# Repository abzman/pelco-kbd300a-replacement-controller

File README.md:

# pelco-kbd300a-replacement-controller
replacement board and code for this joystick and keyboard

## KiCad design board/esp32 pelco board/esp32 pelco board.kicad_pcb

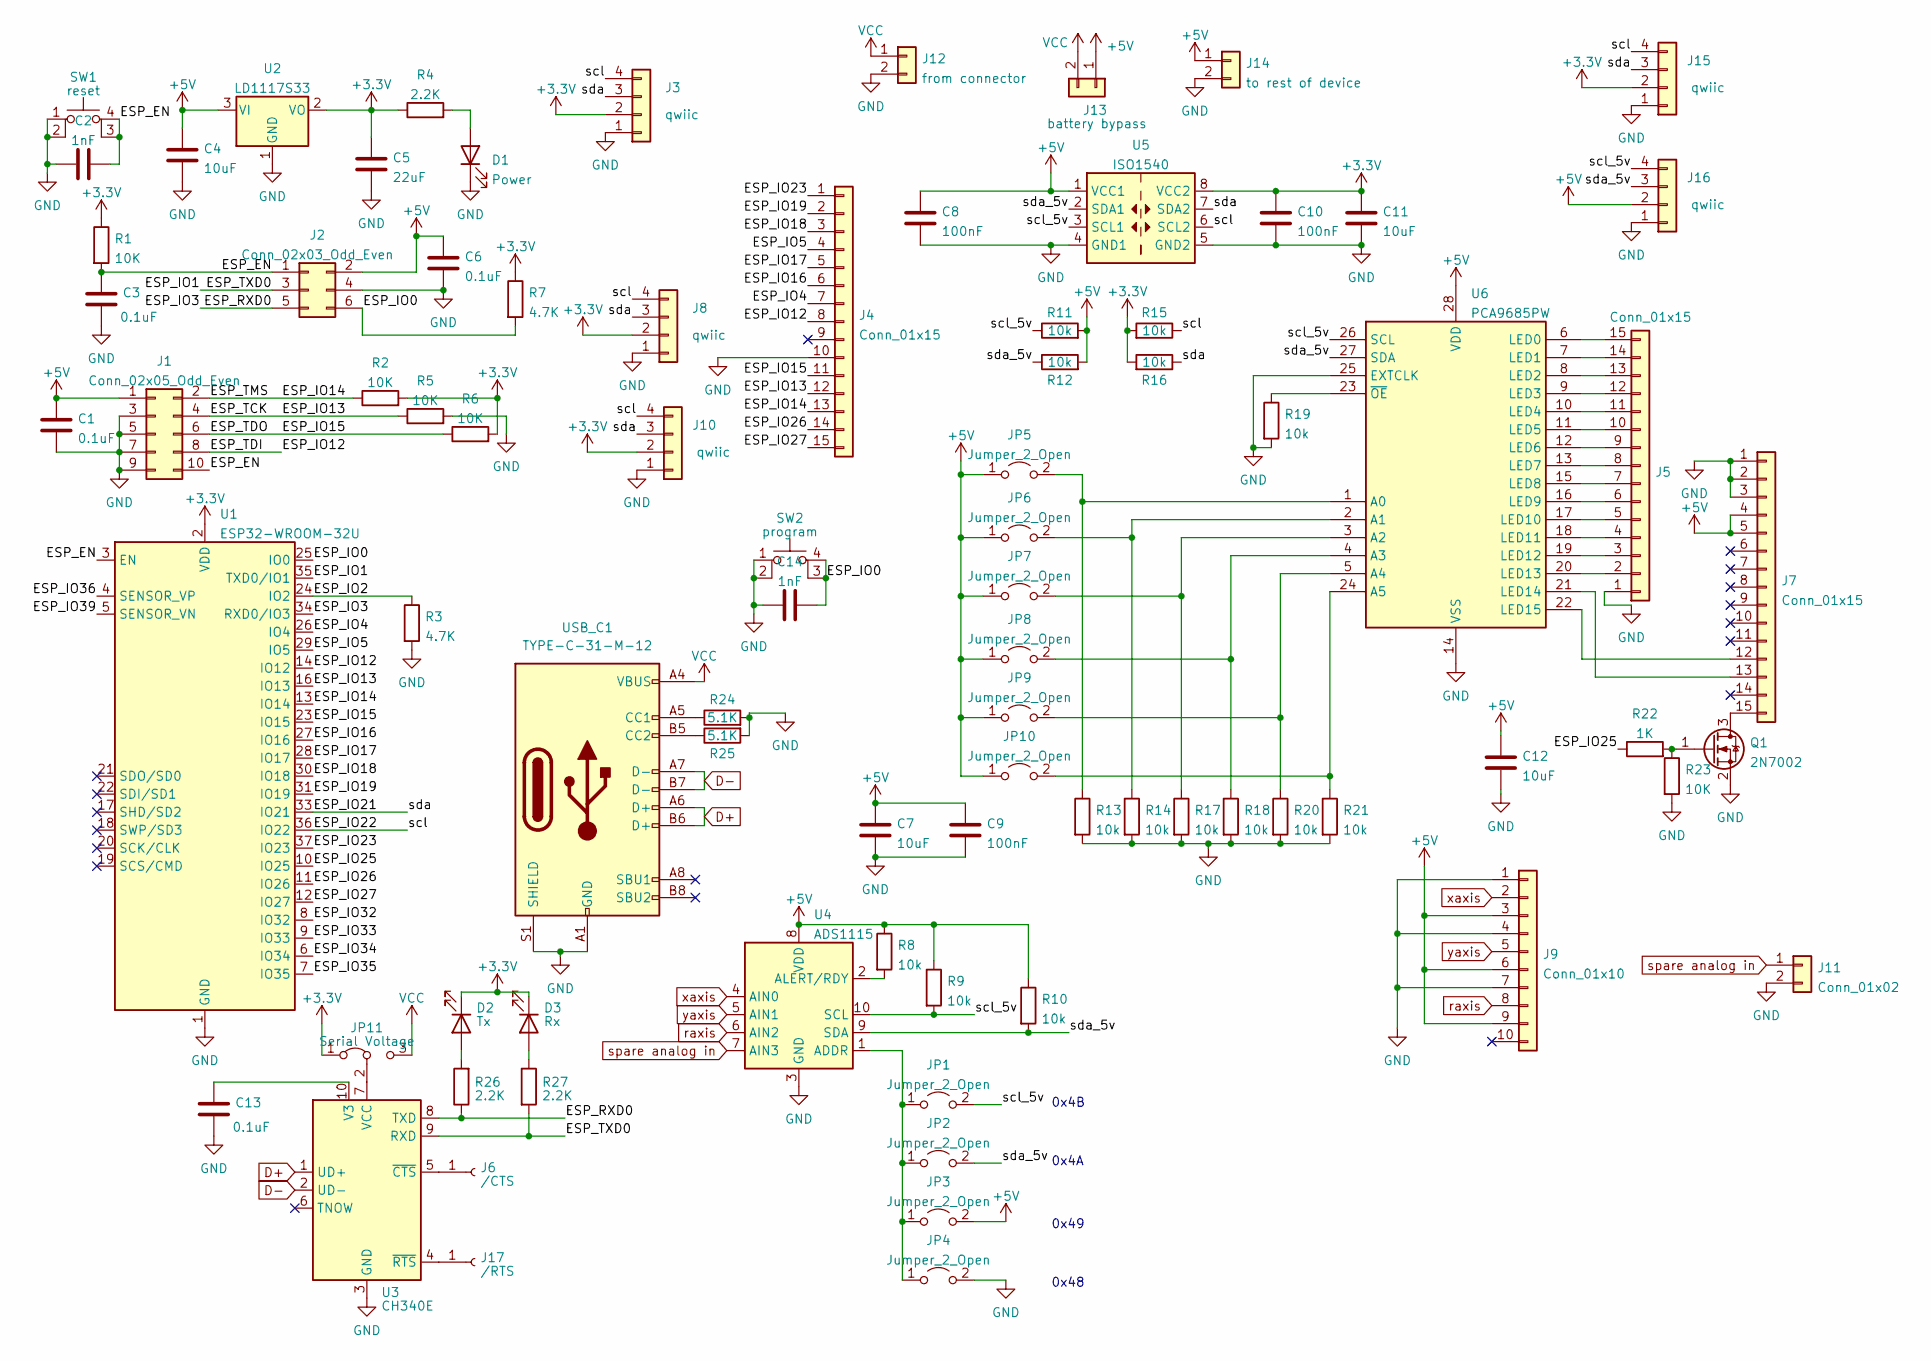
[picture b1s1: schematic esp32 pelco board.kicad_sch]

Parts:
C1, C3, C6, C13: 0.1uF; C_0603_1608Metric
C2, C14: 1nF; C_0603_1608Metric
C4: 10uF; CP_Radial_D5.0mm_P2.00mm
C5: 22uF; CP_Radial_D5.0mm_P2.00mm
C7, C11, C12: 10uF; C_0603_1608Metric
C8, C9, C10: 100nF; C_0603_1608Metric
D1: Power; LED_0603_1608Metric
D2: Tx; LED_0603_1608Metric
D3: Rx; LED_0603_1608Metric
J1: Conn_02x05_Odd_Even; IDC-Header_2x05_P2.54mm_Vertical
J2: Conn_02x03_Odd_Even; IDC-Header_2x03_P2.54mm_Vertical
J3, J8, J10, J15, J16: qwiic; JST_SH_SM04B-SRSS-TB_1x04-1MP_P1.00mm_Horizontal
J4, J5, J7: Conn_01x15; PinHeader_1x15_P2.54mm_Vertical
J6: /CTS; PinSocket_1x01_P2.54mm_Vertical
J9: Conn_01x10; PinHeader_1x10_P2.54mm_Vertical
J11: Conn_01x02; PinHeader_1x02_P2.54mm_Vertical
J12: from connector; PinHeader_1x02_P2.54mm_Vertical
J13: battery bypass; SolderJumper-2_P1.3mm_Bridged_RoundedPad1.0x1.5mm
J14: to rest of device; PinHeader_1x02_P2.54mm_Vertical
J17: /RTS; PinSocket_1x01_P2.54mm_Vertical
JP1, JP2, JP3, JP4, JP5, JP6, JP7, JP8, JP9, JP10: Jumper_2_Open; SolderJumper-2_P1.3mm_Open_RoundedPad1.0x1.5mm
JP11: Serial Voltage; SolderJumper-3_P1.3mm_Bridged12_RoundedPad1.0x1.5mm
Q1: 2N7002; SOT-23
R1, R2, R5, R6, R23: 10K; R_0603_1608Metric
R3, R7: 4.7K; R_0603_1608Metric
R4, R26, R27: 2.2K; R_0603_1608Metric
R8, R9, R10, R11, R12, R13, R14, R15, R16, R17, R18, R19, R20, R21: 10k; R_0603_1608Metric
R22: 1K; R_0603_1608Metric
R24, R25: 5.1K; R_0603_1608Metric
SW1: reset; SW_TH_Tactile_Omron_B3F-10xx
SW2: program; SW_TH_Tactile_Omron_B3F-10xx
U1: ESP32-WROOM-32U
U2: LD1117S33; SOT-223-3_TabPin2
U3: CH340E; MSOP-10_3x3mm_P0.5mm
U4: ADS1115; TSSOP-10_3x3mm_P0.5mm
U5: ISO1540; SOIC-8_3.9x4.9mm_P1.27mm
U6: PCA9685PW; TSSOP-28_4.4x9.7mm_P0.65mm
USB_C1: TYPE-C-31-M-12; USB_C_Receptacle_HRO_TYPE-C-31-M-12; LCSC C165948

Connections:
+3V3: C5.1, C10.1, C11.1, D2.1 (K), D3.1 (K), J3.2, J8.2, J10.2, J15.2, JP11.1 (A), R1.1, R2.2, R4.1, R6.2, R7.1, R15.2, R16.2, U1.2 (VDD), U2.2 (VO), U5.8 (VCC2)
+5V: C1.1, C4.1, C6.1, C7.1, C8.1, C9.1, C12.1, J1.1, J2.2, J7.4, J7.5, J9.3, J9.6, J9.9, J13.1, J14.1, J16.2, JP3.2 (B), JP5.1 (A), JP6.1 (A), JP7.1 (A), JP8.1 (A), JP9.1 (A), JP10.1 (A), R8.1, R9.1, R10.1, R11.2, R12.2, U2.3 (VI), U4.8 (VDD), U5.1 (VCC1), U6.28 (VDD)
/ESP_EN: C2.2, C3.1, J1.10, J2.1, R1.2, SW1.3 (K), SW1.4 (A), U1.3 (EN)
/ESP_IO0: C14.2, J2.6, R7.2, SW2.3 (K), SW2.4 (A), U1.25 (IO0)
/ESP_IO1: J2.3, R27.2, U1.35 (TXD0/IO1), U3.9 (RXD)
/ESP_IO2: R3.1, U1.24 (IO2)
/ESP_IO3: J2.5, R26.1, U1.34 (RXD0/IO3), U3.8 (TXD)
/ESP_IO4: J4.7, U1.26 (IO4)
/ESP_IO5: J4.4, U1.29 (IO5)
/ESP_IO12: J1.8, J4.8, U1.14 (IO12)
/ESP_IO13: J1.4, J4.12, R5.1, U1.16 (IO13)
/ESP_IO14: J1.2, J4.13, R2.1, U1.13 (IO14)
/ESP_IO15: J1.6, J4.11, R6.1, U1.23 (IO15)
/ESP_IO16: J4.6, U1.27 (IO16)
/ESP_IO17: J4.5, U1.28 (IO17)
/ESP_IO18: J4.3, U1.30 (IO18)
/ESP_IO19: J4.2, U1.31 (IO19)
/ESP_IO21: J3.3, J8.3, J10.3, J15.3, R16.1, U1.33 (IO21), U5.7 (SDA2)
/ESP_IO22: J3.4, J8.4, J10.4, J15.4, R15.1, U1.36 (IO22), U5.6 (SCL2)
/ESP_IO23: J4.1, U1.37 (IO23)
/ESP_IO25: R22.1, U1.10 (IO25)
/ESP_IO26: J4.14, U1.11 (IO26)
/ESP_IO27: J4.15, U1.12 (IO27)
/ESP_IO32: U1.8 (IO32)
/ESP_IO33: U1.9 (IO33)
/ESP_IO34: U1.6 (IO34)
/ESP_IO35: U1.7 (IO35)
/ESP_IO36: U1.4 (SENSOR_VP)
/ESP_IO39: U1.5 (SENSOR_VN)
/scl_5v: J16.4, JP1.2 (B), R9.2, R11.1, U4.10 (SCL), U5.3 (SCL1), U6.26 (SCL)
/sda_5v: J16.3, JP2.2 (B), R10.2, R12.1, U4.9 (SDA), U5.2 (SDA1), U6.27 (SDA)
D+: U3.1 (UD+), USB_C1.A6 (D+), USB_C1.B6 (D+)
D-: U3.2 (UD-), USB_C1.A7 (D-), USB_C1.B7 (D-)
GND: C1.2, C2.1, C3.2, C4.2, C5.2, C6.2, C7.2, C8.2, C9.2, C10.2, C11.2, C12.2, C13.2, C14.1, D1.1 (K), J1.3, J1.5, J1.7, J1.9, J2.4, J3.1, J3.MP, J4.10, J5.1, J7.1, J7.2, J7.3, J8.1, J8.MP, J9.1, J9.4, J9.7, J10.1, J10.MP, J11.2, J12.2, J14.2, J15.1, J15.MP, J16.1, J16.MP, JP4.2 (B), Q1.2 (S), R3.2, R5.2, R13.2, R14.2, R17.2, R18.2, R19.2, R20.2, R21.2, R23.2, R24.2, R25.2, SW1.1, SW1.2, SW2.1, SW2.2, U1.1 (GND), U1.15 (GND), U1.38 (GND), U1.39 (GND), U2.1 (GND), U3.3 (GND), U4.3 (GND), U5.4 (GND1), U5.5 (GND2), U6.14 (VSS), U6.25 (EXTCLK), USB_C1.A1 (GND), USB_C1.A12 (GND), USB_C1.B1 (GND), USB_C1.B12 (GND), USB_C1.S1 (SHIELD)
unnamed: D1.2 (A), R4.2
unnamed: D2.2 (A), R26.2
unnamed: D3.2 (A), R27.1
unnamed: J5.2, U6.20 (LED13)
unnamed: J5.3, U6.19 (LED12)
unnamed: J5.4, U6.18 (LED11)
unnamed: J5.5, U6.17 (LED10)
unnamed: J5.6, U6.16 (LED9)
unnamed: J5.7, U6.15 (LED8)
unnamed: J5.8, U6.13 (LED7)
unnamed: J5.9, U6.12 (LED6)
unnamed: J5.10, U6.11 (LED5)
unnamed: J5.11, U6.10 (LED4)
unnamed: J5.12, U6.9 (LED3)
unnamed: J5.13, U6.8 (LED2)
unnamed: J5.14, U6.7 (LED1)
unnamed: J5.15, U6.6 (LED0)
unnamed: J6.1, U3.5 (~CTS)
unnamed: J7.12, U6.22 (LED15)
unnamed: J7.13, U6.21 (LED14)
unnamed: J7.15, Q1.3 (D)
unnamed: J17.1, U3.4 (~RTS)
unnamed: JP1.1 (A), JP2.1 (A), JP3.1 (A), JP4.1 (A), U4.1 (ADDR)
unnamed: JP5.2 (B), R13.1, U6.1 (A0)
unnamed: JP6.2 (B), R14.1, U6.2 (A1)
unnamed: JP7.2 (B), R17.1, U6.3 (A2)
unnamed: JP8.2 (B), R18.1, U6.4 (A3)
unnamed: JP9.2 (B), R20.1, U6.5 (A4)
unnamed: JP10.2 (B), R21.1, U6.24 (A5)
unnamed: JP11.2 (C), U3.7 (VCC)
unnamed: Q1.1 (G), R22.2, R23.1
unnamed: C13.1, U3.10 (V3)
unnamed: R8.2, U4.2 (ALERT/RDY)
unnamed: R19.1, U6.23 (~OE)
unnamed: R24.1, USB_C1.A5 (CC1)
unnamed: R25.1, USB_C1.B5 (CC2)
VCC: J12.1, J13.2, JP11.3 (B), USB_C1.A4 (VBUS), USB_C1.A9 (VBUS), USB_C1.B4 (VBUS), USB_C1.B9 (VBUS)
raxis: J9.8, U4.6 (AIN2)
spare analog in: J11.1, U4.7 (AIN3)
xaxis: J9.2, U4.4 (AIN0)
yaxis: J9.5, U4.5 (AIN1)

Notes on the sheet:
0x48
0x49
0x4B
0x4A

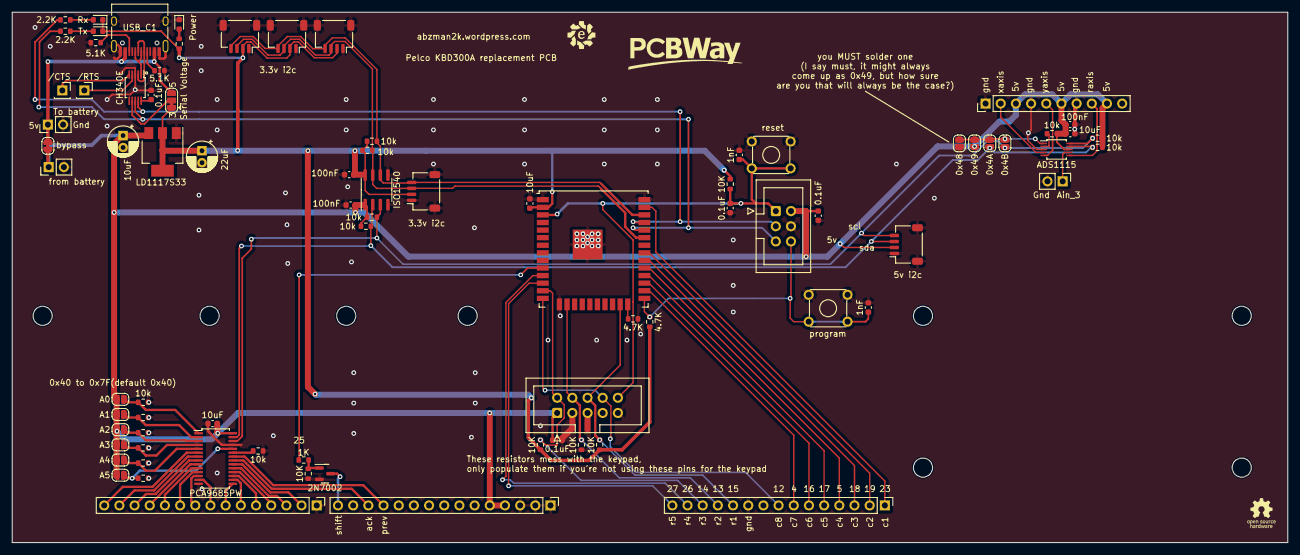
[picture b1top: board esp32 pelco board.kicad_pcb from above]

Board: 2 copper layers, 213.4 x 88.7 mm, 82 parts (0 on the bottom side), 69 nets.

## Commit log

2023-03-08 board design done
2023-05-16 added usb serial and programming button
2023-12-02 updated gitignore and board tweaks
2023-12-02 added pcbway logo
2023-12-02 added first rev of integrated code and libraries
2023-12-02 added last library
2023-12-09 added pdf schematic
2023-12-13 tweak design based on fixes
2023-12-13 remove backup
2023-12-14 tweaks to silk and new gerbers
2025-06-13 added silk assembly note
2025-06-15 fixed silk
